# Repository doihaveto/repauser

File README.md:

# Repauser

USB-HID device based on attiny85.

The intended use of this device is to pause movies (press the space key) when the user rises from his chair, using a force-sensing resistor connected to the chair and the device.

## Schematic ##

Included in this project:

 - Source code
 - Kicad project files
 - Fabrication-ready board image files

## Flashing instructions ###
I used USBASP to flash the code the attiny85, and AVRDUDE. The makefile included in this project uses AVRDUDE.

Default fuses (required for reflashing):
```avrdude -p attiny85 -c usbasp -U lfuse:w:0x62:m -U hfuse:w:0xdf:m -U efuse:w:0xff:m```
Reading fuses:
```avrdude -p attiny85 -c usbasp -U lfuse:r:-:h -U hfuse:r:-:h -U efuse:r:-:h```

Compiling and flashing:
```
make
make resetfuses
make flash
make setfuses
```

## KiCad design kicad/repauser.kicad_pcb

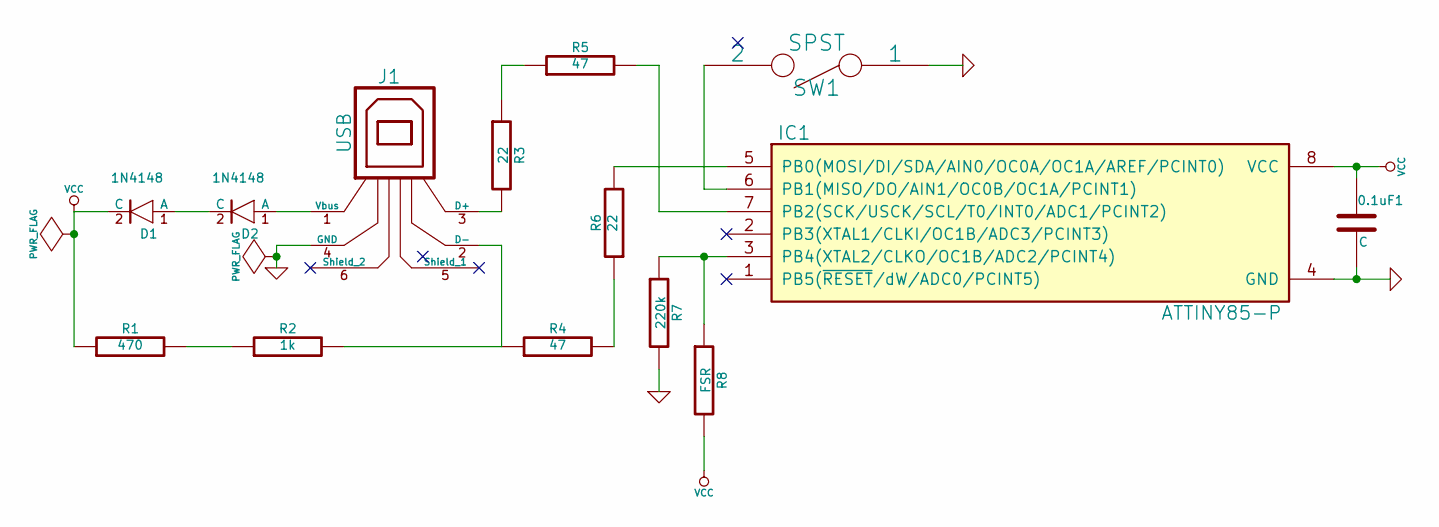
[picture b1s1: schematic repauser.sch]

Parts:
0.1uF1: C
D1, D2: 1N4148; DO35
IC1: ATTINY85-P; DIP8
J1: USB
R1: 470
R2: 1k
R3, R6: 22
R4, R5: 47
R7: 220k
R8: FSR
SW1: SPST

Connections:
GND: 0.1uF1.2, IC1.4 (GND), J1.4 (GND), R7.2, SW1.1
unnamed: J1.2 (D-), R2.2, R4.1
unnamed: J1.3 (D+), R3.2
unnamed: R3.1, R5.1
unnamed: IC1.7 (PB2(SCK/USCK/SCL/T0/INT0/ADC1/PCINT2)), R5.2
unnamed: IC1.5 (PB0(MOSI/DI/SDA/AIN0/OC0A/OC1A/AREF/PCI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), R6.2
unnamed: R4.2, R6.1
unnamed: R1.2, R2.1
unnamed: IC1.6 (PB1(MISO/DO/AIN1/OC0B/OC1A/PCINT1)), SW1.2
unnamed: IC1.3 (PB4(XTAL2/CLKO/OC1B/ADC2/PCINT4)), R7.1, R8.1
unnamed: D1.1 (A), D2.2 (C)
unnamed: D2.1 (A), J1.1 (Vbus)
VCC: 0.1uF1.1, D1.2 (C), IC1.8 (VCC), R1.1, R8.2

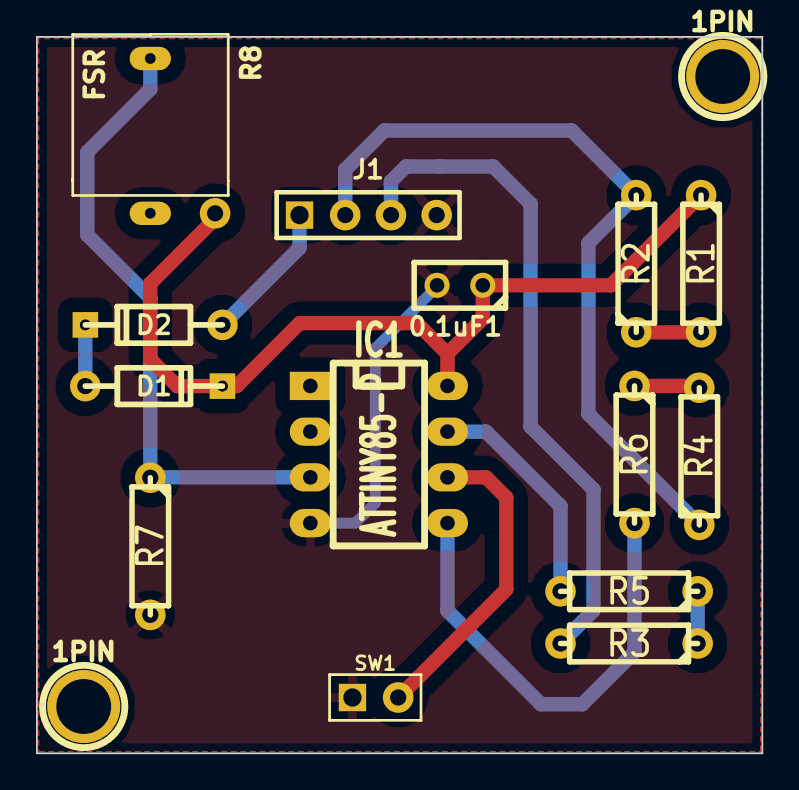
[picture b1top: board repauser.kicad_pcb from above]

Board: 2 copper layers, 40.3 x 39.8 mm, 16 parts (0 on the bottom side), 13 nets.

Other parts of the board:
1PIN, 1PIN#2: P***; 1pin

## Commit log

2016-09-21 Project info
